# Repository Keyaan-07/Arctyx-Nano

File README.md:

# Arctyx Nano

Arctyx Nano is an FPGA development board carrying the ICE40UP5K FPGA from Lattice. It also carries RP2350A from Raspberry Pi.  

Check out the board on [KiCanvas](https://kicanvas.org/?github=https://github.com/Keyaan-07/Arctyx-Nano/tree/main/hardware_Arctyx-Nano)

## Features:
> Dual core ARM Cortex-M33 Processor (also everything else the RP2350 has)  
> 8 channel bus connecting the FPGA and the RP2350A  
> 128Mbit of Flash.  
> 6 General Purpose LEDs (4x for FPGA and 2x for RP2350A).  
> RGB LED connected to the FPGA.  
> Onboard Dual Stepdown Convertor.    
> USB Boot Button for RP2350A.  

## IO Pin mapping:

| Programmer Pin | Pin on FPGA     | Pin on RP2350A |
| -------------- | --------------- | -------------- |
| CSn            | IOB_35b_SPI_SS  | GPIO17         |
| MOSI           | IOB_33b_SPI_SI  | GPIO19         |
| MISO           | IOB_32a_SPI_SO  | GPIO20         |
| SCLK           | IOB_34a_SPI_SCK | GPIO18         |

| Pin Label | Pin on FPGA | Pin label | Pin on FPGA |
| --------- | ----------- | --------- | ----------- |
| IO1       | IOT_41a     | IO11      | IOB_4a      |
| IO2       | IOT_42b     | IO12      | IOB_6a      |
| IO3       | IOT_43a     | IO13      | IOB_9b      |
| IO4       | IOT_44b     | IO14      | IOB_9a      |
| IO5       | IOT_46b     | IO15      | IOB_13b     |
| IO6       | IOT_48b     | IO16      | IOB_16a     |
| IO7       | IOT_45a     | IO17      | IOB_18a     |
| IO8       | IOT_50b     | IO18      | IOB_20a     |
| IO9       | IOT_51a     | IO19      | IOB_22a     |
| IO10      | IOT_49a     | IO20      | IOB_24a     |

| BUS Pin | Pin on FPGA | Pin on RP2350A |
| ------- | ----------- | -------------- |
| BUS0    | IOT_38b     | GPIO9          |
| BUS1    | IOT_39a     | GPIO10         |
| BUS2    | IOT_36b     | GPIO11         |
| BUS3    | IOT_37a     | GPIO12         |
| BUS4    | IOB_23b     | GPIO13         |
| BUS5    | IOB_25b_G3  | GPIO14         |
| BUS6    | IOB_29b     | GPIO15         |
| BUS7    | IOB_31b     | GPIO16         |

| LED | Pin On FPGA/MCU  |
| --- | ---------------  |
| D1  | IOB_0a           |
| D2  | IOB_2a           |
| D3  | IOB_5b           |
| D4  | IOB_3b_G6        |
| D5  | GPIO21           |
| D6  | GPIO22           |
| RGB | RGB0, RGB1, RGB2 |

## BOM
| Item              | Cost  | Note               |
| ----------------- | ----- | ------------------ |
| PCB               | 17.8  | 4-Layers           |
| PCBA              | 52.77 | Kinda Dense board  |
| Shipping charges  | 9.28  |                    |
| coupon Discount   | \-9   |                    |
| Total             | 70.85 | USD                |

### PCB Components Breakdown
| Designator                                          | Designation                 | Footprint                                | Quantity | Amount | JLCPCB Lib type | JLCPCB Part Number |
| --------------------------------------------------- | --------------------------- | ---------------------------------------- | -------- | ------ | --------------- | ------------------ |
| C1,C2                                               | 15p                         | 0402                                     | 4        | 0.004  | Basic           | C1548              |
| C10,C11,C12,C13,C14,C15,C17,C18,C19,C21,C6,C7,C8,C9 | 100n                        | 0402                                     | 28       | 0.0336 | Basic           | C1525              |
| C16,C23,C3,C4,C5                                    | 4.7u                        | 0402                                     | 10       | 0.049  | Basic           | C23733             |
| C20,C22                                             | 22u                         | 0603                                     | 4        | 0.0348 | Basic           | C59461             |
| C24                                                 | 10u                         | 0603                                     | 2        | 0.0112 | Basic           | C19702             |
| D1,D2,D3,D4,D5,D6                                   | LED                         | 0603                                     | 12       | 0.1224 | Extended        | C2290            |
| L1,L2,L3                                            | AOTA-B201610S3R3-101-T      | IND-SMD_L2.0-W1.6_AOTA-B201610S3R3-101-T | 6        | 1.0782 | Extended        | C42411119          |
| R1,R2                                               | 5.1k                        | 0402                                     | 4        | 0.002  | Basic           | C25905             |
| R3,R4                                               | 27                          | 0402                                     | 20       | 0.012  | Extended        | C138021            |
| R5,R7                                               | 1k                          | 0402                                     | 4        | 0.0024 | Basic           | C11702             |
| R6                                                  | 33                          | 0402                                     | 2        | 0.0012 | Basic           | C25105             |
| R10,R9                                              | 51k                         | 0402                                     | 4        | 0.0024 | Basic           | C25794             |
| R11                                                 | 100k                        | 0402                                     | 2        | 0.0012 | Basic           | C25741             |
| R12                                                 | 22k                         | 0402                                     | 2        | 0.0012 | Basic           | C25768             |
| R13                                                 | 120                         | 0402                                     | 2        | 0.0012 | Basic           | C25079             |
| R14,R15,R16,R17,R18,R19,R20,R21                     | 100                         | 0402                                     | 16       | 0.008  | Basic           | C25076             |
| SW1                                                 | SW_Push                     | SW-SMD_L3.9-W3.0-P4.45                   | 2        | 0.0846 | Basic           | C720477            |
| U1                                                  | ICE40UP5K-SG48ITR           | QFN-48-1EP_7x7mm_P0.5mm_EP5.6x5.6mm      | 2        | 11.352 | Extended        | C2678152           |
| U2                                                  | RP2350A-QFN60               | RP2350A_QFN-60_EP_7.75x7.75_Pitch0.4mm   | 2        | 3.195  | Extended        | C42411118          |
| U3                                                  | W25Q128JVP                  | WSON-8-1EP_6x5mm_P1.27mm_EP3.4x4.3mm     | 2        | 2.472  | Extended        | C2441427           |
| U4                                                  | RT8075ZQW                   | WDFN-10_L3.0-W3.0-P0.50-BL-EP            | 2        | 0.864  | Extended        | C250416            |
| U5                                                  | TJ-S1608SW6TDSLCCYRGB-A5    | LED-ARRAY-SMD_4P-L1.6-W0.8-BL-FD         | 6        | 0.4314 | Extended        | C5356078           |
| Y1                                                  | Crystal_GND24               | Crystal_SMD_3225-4Pin_3.2x2.5mm          | 2        | 0.1290  | Basic        | C9002          |
| J1                                                  | USB_C_Receptacle_USB2.0_16P | USB_C_Receptacle_XKB_U262-16XN-4BVC11    | 0        | 0      | Do Not Place    | Do Not Place       |

## License and Contribution

[MIT License](/LICENSE)

Open to contributions in both software and hardware!

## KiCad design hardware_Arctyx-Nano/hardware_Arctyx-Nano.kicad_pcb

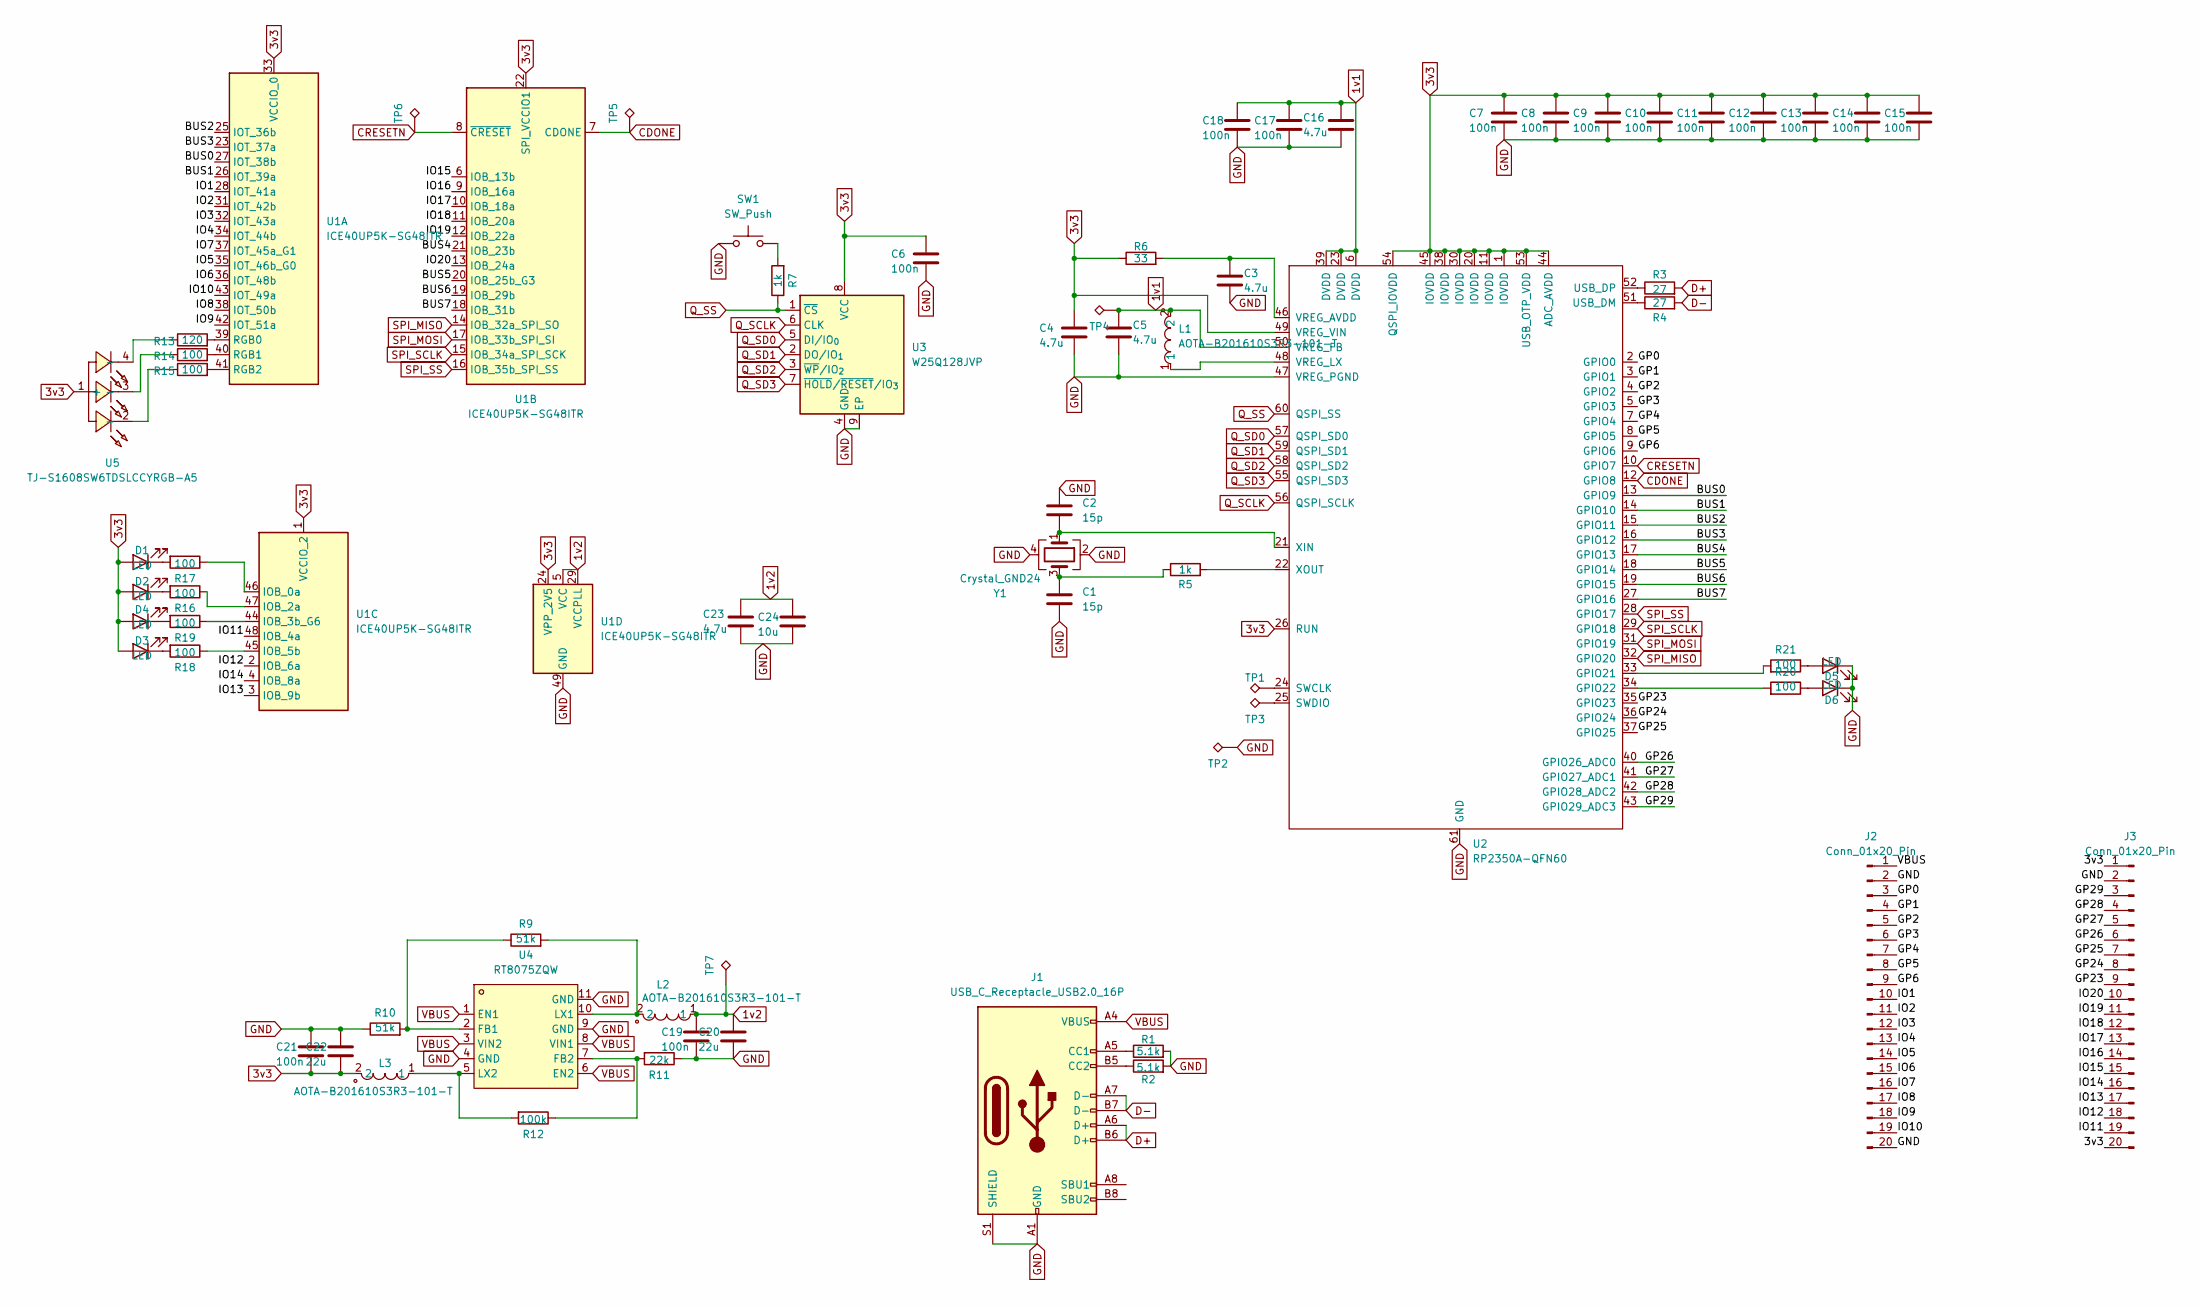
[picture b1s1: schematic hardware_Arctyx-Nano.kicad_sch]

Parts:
C1, C2: 15p; C_0402_1005Metric
C3, C4, C5, C16, C23: 4.7u; C_0402_1005Metric
C6, C7, C8, C9, C10, C11, C12, C13, C14, C15, C17, C18, C19, C21: 100n; C_0402_1005Metric
C20, C22: 22u; C_0603_1608Metric
C24: 10u; C_0603_1608Metric
D1, D2, D3, D4, D5, D6: LED; LED_0603_1608Metric
J1: USB_C_Receptacle_USB2.0_16P; USB_C_Receptacle_XKB_U262-16XN-4BVC11
J2, J3: Conn_01x20_Pin; PinHeader_1x20_P2.54mm_Vertical
L1, L2, L3: AOTA-B201610S3R3-101-T; IND-SMD_L2.0-W1.6_AOTA-B201610S3R3-101-T; LCSC Part C42411119
R1, R2: 5.1k; R_0402_1005Metric
R3, R4: 27; R_0402_1005Metric
R5, R7: 1k; R_0402_1005Metric
R6: 33; R_0402_1005Metric
R9, R10: 51k; R_0402_1005Metric
R11: 22k; R_0402_1005Metric
R12: 100k; R_0402_1005Metric
R13: 120; R_0402_1005Metric
R14, R15, R16, R17, R18, R19, R20, R21: 100; R_0402_1005Metric
SW1: SW_Push; SW-SMD_L3.9-W3.0-P4.45
TP1, TP2, TP3, TP4, TP5, TP6, TP7: TestPoint_Alt; TestPoint_Pad_D1.0mm
U1: ICE40UP5K-SG48ITR; QFN-48-1EP_7x7mm_P0.5mm_EP5.6x5.6mm
U2: RP2350A-QFN60; RP2350A_QFN-60_EP_7.75x7.75_Pitch0.4mm
U3: W25Q128JVP; WSON-8-1EP_6x5mm_P1.27mm_EP3.4x4.3mm
U4: RT8075ZQW; WDFN-10_L3.0-W3.0-P0.50-BL-EP; LCSC Part C250416
U5: TJ-S1608SW6TDSLCCYRGB-A5; LED-ARRAY-SMD_4P-L1.6-W0.8-BL-FD; LCSC Part C5356078
Y1: Crystal_GND24; Crystal_SMD_3225-4Pin_3.2x2.5mm

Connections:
1v1: C5.1, C16.1, C17.1, C18.1, L1.2, TP4.1, U2.6 (DVDD), U2.23 (DVDD), U2.39 (DVDD), U2.50 (VREG_FB)
1v2: C19.1, C20.1, C23.1, C24.1, L2.1, TP7.1, U1.5 (VCC), U1.29 (VCCPLL), U1.30 (VCC)
3v3: C4.1, C6.1, C7.1, C8.1, C9.1, C10.1, C11.1, C12.1, C13.1, C14.1, C15.1, C21.2, C22.2, D1.2 (A), D2.2 (A), D3.2 (A), D4.2 (A), J3.1, J3.20, L3.2, R6.1, U1.1 (VCCIO_2), U1.22 (SPI_VCCIO1), U1.24 (VPP_2V5), U1.33 (VCCIO_0), U2.1 (IOVDD), U2.11 (IOVDD), U2.20 (IOVDD), U2.26 (RUN), U2.30 (IOVDD), U2.38 (IOVDD), U2.44 (ADC_AVDD), U2.45 (IOVDD), U2.49 (VREG_VIN), U2.53 (USB_OTP_VDD), U2.54 (QSPI_IOVDD), U3.8 (VCC), U5.1 (+)
/BUS0: U1.27 (IOT_38b), U2.13 (GPIO9)
/BUS1: U1.26 (IOT_39a), U2.14 (GPIO10)
/BUS2: U1.25 (IOT_36b), U2.15 (GPIO11)
/BUS3: U1.23 (IOT_37a), U2.16 (GPIO12)
/BUS4: U1.21 (IOB_23b), U2.17 (GPIO13)
/BUS5: U1.20 (IOB_25b_G3), U2.18 (GPIO14)
/BUS6: U1.19 (IOB_29b), U2.19 (GPIO15)
/BUS7: U1.18 (IOB_31b), U2.27 (GPIO16)
/GP0: J2.3, U2.2 (GPIO0)
/GP1: J2.4, U2.3 (GPIO1)
/GP2: J2.5, U2.4 (GPIO2)
/GP3: J2.6, U2.5 (GPIO3)
/GP4: J2.7, U2.7 (GPIO4)
/GP5: J2.8, U2.8 (GPIO5)
/GP6: J2.9, U2.9 (GPIO6)
/GP23: J3.9, U2.35 (GPIO23)
/GP24: J3.8, U2.36 (GPIO24)
/GP25: J3.7, U2.37 (GPIO25)
/GP26: J3.6, U2.40 (GPIO26_ADC0)
/GP27: J3.5, U2.41 (GPIO27_ADC1)
/GP28: J3.4, U2.42 (GPIO28_ADC2)
/GP29: J3.3, U2.43 (GPIO29_ADC3)
/IO1: J2.10, U1.28 (IOT_41a)
/IO2: J2.11, U1.31 (IOT_42b)
/IO3: J2.12, U1.32 (IOT_43a)
/IO4: J2.13, U1.34 (IOT_44b)
/IO5: J2.14, U1.35 (IOT_46b_G0)
/IO6: J2.15, U1.36 (IOT_48b)
/IO7: J2.16, U1.37 (IOT_45a_G1)
/IO8: J2.17, U1.38 (IOT_50b)
/IO9: J2.18, U1.42 (IOT_51a)
/IO10: J2.19, U1.43 (IOT_49a)
/IO11: J3.19, U1.48 (IOB_4a)
/IO12: J3.18, U1.2 (IOB_6a)
/IO13: J3.17, U1.3 (IOB_9b)
/IO14: J3.16, U1.4 (IOB_8a)
/IO15: J3.15, U1.6 (IOB_13b)
/IO16: J3.14, U1.9 (IOB_16a)
/IO17: J3.13, U1.10 (IOB_18a)
/IO18: J3.12, U1.11 (IOB_20a)
/IO19: J3.11, U1.12 (IOB_22a)
/IO20: J3.10, U1.13 (IOB_24a)
CDONE: TP5.1, U1.7 (CDONE), U2.12 (GPIO8)
CRESETN: TP6.1, U1.8 (~CRESET), U2.10 (GPIO7)
D+: J1.A6 (D+), J1.B6 (D+), R3.2
D-: J1.A7 (D-), J1.B7 (D-), R4.2
GND: C1.2, C2.1, C3.2, C4.2, C5.2, C6.2, C7.2, C8.2, C9.2, C10.2, C11.2, C12.2, C13.2, C14.2, C15.2, C16.2, C17.2, C18.2, C19.2, C20.2, C21.1, C22.1, C23.2, C24.2, D5.1 (K), D6.1 (K), J1.A1 (GND), J1.A12 (GND), J1.B1 (GND), J1.B12 (GND), J1.S1 (SHIELD), J2.2, J2.20, J3.2, R1.2, R2.2, R10.1, R11.1, SW1.1, TP2.1, U1.49 (GND), U2.47 (VREG_PGND), U2.61 (GND), U3.4 (GND), U3.9 (EP), U4.4 (GND), U4.9 (GND), U4.11 (GND), Y1.2, Y1.4
unnamed: C1.1, R5.1, Y1.3
unnamed: D1.1 (K), R17.2
unnamed: D2.1 (K), R16.2
unnamed: D3.1 (K), R18.2
unnamed: D4.1 (K), R19.2
unnamed: D5.2 (A), R21.1
unnamed: D6.2 (A), R20.1
unnamed: J1.A5 (CC1), R1.1
unnamed: J1.B5 (CC2), R2.1
unnamed: R7.2, SW1.2
unnamed: R13.1, U5.4 (-)
unnamed: R14.1, U5.3 (-)
unnamed: R15.1, U5.2 (-)
unnamed: R13.2, U1.39 (RGB0)
unnamed: R14.2, U1.40 (RGB1)
unnamed: R15.2, U1.41 (RGB2)
unnamed: R17.1, U1.46 (IOB_0a)
unnamed: R16.1, U1.47 (IOB_2a)
unnamed: R19.1, U1.44 (IOB_3b_G6)
unnamed: R18.1, U1.45 (IOB_5b)
unnamed: R21.2, U2.33 (GPIO21)
unnamed: R20.2, U2.34 (GPIO22)
unnamed: TP1.1, U2.24 (SWCLK)
unnamed: TP3.1, U2.25 (SWDIO)
unnamed: R4.1, U2.51 (USB_DM)
unnamed: R3.1, U2.52 (USB_DP)
unnamed: C3.1, R6.2, U2.46 (VREG_AVDD)
unnamed: L1.1, U2.48 (VREG_LX)
unnamed: C2.2, U2.21 (XIN), Y1.1
unnamed: R5.2, U2.22 (XOUT)
unnamed: R9.1, R10.2, U4.2 (FB1)
unnamed: R11.2, R12.1, U4.7 (FB2)
unnamed: L2.2, R9.2, U4.10 (LX1)
unnamed: L3.1, R12.2, U4.5 (LX2)
Q_SCLK: U2.56 (QSPI_SCLK), U3.6 (CLK)
Q_SD0: U2.57 (QSPI_SD0), U3.5 (DI/IO_{0})
Q_SD1: U2.59 (QSPI_SD1), U3.2 (DO/IO_{1})
Q_SD2: U2.58 (QSPI_SD2), U3.3 (~WP/IO_{2})
Q_SD3: U2.55 (QSPI_SD3), U3.7 (~HOLD/~RESET/IO_{3})
Q_SS: R7.1, U2.60 (QSPI_SS), U3.1 (~CS)
SPI_MISO: U1.14 (IOB_32a_SPI_SO), U2.32 (GPIO20)
SPI_MOSI: U1.17 (IOB_33b_SPI_SI), U2.31 (GPIO19)
SPI_SCLK: U1.15 (IOB_34a_SPI_SCK), U2.29 (GPIO18)
SPI_SS: U1.16 (IOB_35b_SPI_SS), U2.28 (GPIO17)
VBUS: J1.A4 (VBUS), J1.A9 (VBUS), J1.B4 (VBUS), J1.B9 (VBUS), J2.1, U4.1 (EN1), U4.3 (VIN2), U4.6 (EN2), U4.8 (VIN1)

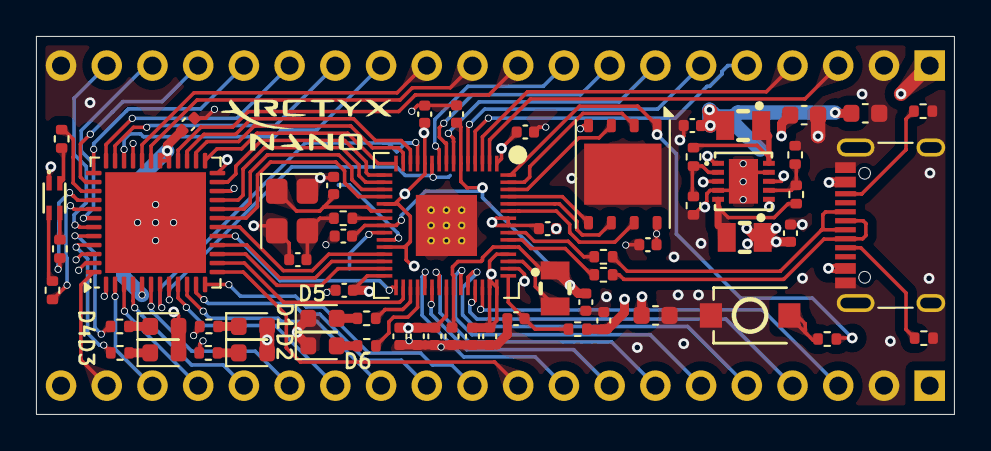
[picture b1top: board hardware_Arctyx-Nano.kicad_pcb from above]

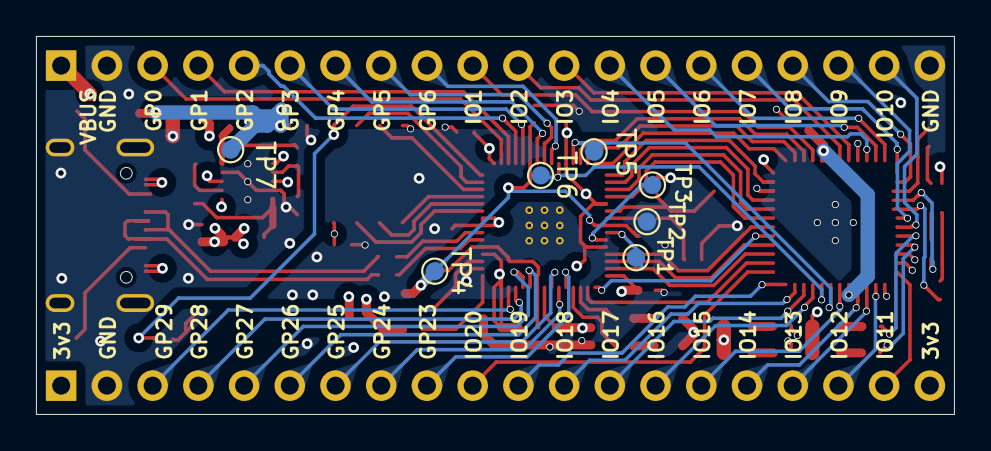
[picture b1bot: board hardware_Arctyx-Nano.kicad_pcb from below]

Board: 4 copper layers, 51.0 x 21.0 mm, 70 parts (9 on the bottom side), 95 nets.

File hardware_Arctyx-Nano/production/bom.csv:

Designator,Footprint,Quantity,Value,LCSC Part #
"C1, C2",0402,2,15p,
"C10, C11, C12, C13, C14, C15, C17, C18, C19, C21, C6, C7, C8, C9",0402,14,100n,
"C16, C23, C3, C4, C5",0402,5,4.7u,
"C20, C22",0603,2,22u,
C24,0603,1,10u,
"D1, D2, D3, D4, D5, D6",0603,6,LED,
J1,USB_C_Receptacle_XKB_U262-16XN-4BVC11,1,USB_C_Receptacle_USB2.0_16P,
"J2, J3",PinHeader_1x20_P2.54mm_Vertical,2,Conn_01x20_Pin,
"L1, L2, L3",IND-SMD_L2.0-W1.6_AOTA-B201610S3R3-101-T,3,AOTA-B201610S3R3-101-T,C42411119
"R1, R2",0402,2,5.1k,
"R10, R9",0402,2,51k,
R11,0402,1,22k,
R12,0402,1,100k,
R13,0402,1,120,
"R14, R15, R16, R17, R18, R19, R20, R21",0402,8,100,
"R3, R4",0402,2,27,
"R5, R7",0402,2,1k,
R6,0402,1,33,
SW1,SW-SMD_L3.9-W3.0-P4.45,1,SW_Push,
"TP1, TP2, TP3, TP4, TP5, TP6, TP7",TestPoint_Pad_D1.0mm,7,TestPoint_Alt,
U1,QFN-48-1EP_7x7mm_P0.5mm_EP5.6x5.6mm,1,ICE40UP5K-SG48ITR,
U2,RP2350A_QFN-60_EP_7.75x7.75_Pitch0.4mm,1,RP2350A-QFN60,
U3,WSON-8-1EP_6x5mm_P1.27mm_EP3.4x4.3mm,1,W25Q128JVP,
U4,WDFN-10_L3.0-W3.0-P0.50-BL-EP,1,RT8075ZQW,C250416
U5,LED-ARRAY-SMD_4P-L1.6-W0.8-BL-FD,1,TJ-S1608SW6TDSLCCYRGB-A5,C5356078
Y1,Crystal_SMD_3225-4Pin_3.2x2.5mm,1,Crystal_GND24,

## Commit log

2025-10-13 schematic
2025-10-20 Routing the PCB
2025-10-21 PCB Routing
2025-10-22 Fixing Silkscreen
2025-10-25 removed reference labels
2025-10-25 removed reference labels in PCB
2025-10-25 PCB fixing errors
2025-10-26 production files generation and branding
2025-10-26 fixing rp2350 footprint
2025-10-26 gerber generated
2025-10-26 New Backups
2025-10-29 IO Mapping
2025-10-29 Add LICENSE
2025-10-29 Added BOM
2025-10-29 Fixed minor errors
2025-10-29 ibom
2025-10-29 added 3d model
2025-10-29 BOM.csv added
2025-10-29 firmware - wip
2025-10-30 BOM Optimisation
2025-10-30 Fix LED reference
2025-10-30 Fixed 'It'
2025-10-30 backups
2025-10-30 IO reference changed
2025-12-01 removed jlc checkout page
2025-12-01 upload process
2025-12-01 blink code!
2025-12-01 README
2025-12-01 blink demo video
2025-12-01 change folder name
2025-12-01 added images
2025-12-01 images of assembled PCB added!
2025-12-02 update load capacitor values
2025-12-02 fixed media
2025-12-02 fixed RGB demo
2025-12-03 added PWM example
2025-12-03 PWM gif
2025-12-10 Removed via-in-pad
